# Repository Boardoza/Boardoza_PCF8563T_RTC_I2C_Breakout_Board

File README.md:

# Boardoza PCF8563T RTC Breakout Board

The **Boardoza PCF8563T RTC Breakout Board** is a compact and reliable real-time clock solution built around the **PCF8563T** low-power CMOS clock/calendar IC from NXP. It provides accurate timekeeping with full calendar functionality including year, month, day, weekday, hours, minutes, and seconds. Designed for embedded systems that require dependable time management.

With its simple I²C interface and clearly labeled header pins, this breakout board is fully compatible with Arduino, Raspberry Pi, STM32, ESP32, and other microcontrollers that **support I²C communication**. It is ideal for applications such as **data logging, alarm scheduling, time-stamping systems, industrial controllers, IoT devices, and battery-powered embedded projects.**

> [!WARNING]
> This product does not come with a CR1220 coin cell battery. The battery must be purchased separately.

## [Click here to purchase!](https://www.ozdisan.com/ureticiler/boardoza)

| Front Side | Back Side |
|:---:|:---:|
|  |  |

---

## Key Features

- **Accurate Real-Time Clock:** Maintains precise time and full calendar tracking.
- **I²C Interface:** Simple and widely supported communication with microcontrollers.
- **Interrupt & Clock Output:** Provides **nINT** for alerts and **CLK_O** for clock signal output.
- **Battery Backup Support:** Continues timekeeping during power loss with a coin cell battery.
- **Wide Compatibility:** Works with Arduino, ESP32, STM32, Raspberry Pi, and more.

---

## Technical Specifications

**Model:** PCF8563T  
**Manufacturer:** Boardoza    
**Manufacturer IC:** NXP Semiconductors  
**Input Voltage:** 2.5V – 5.5V DC  
**Functions:** Real-Time Clock & Calendar  
**Communication:** I²C (7-bit address 0x51, Write: A2h, Read: A3h)  
**Oscillator Frequency:** 32.768 kHz  
**Operating Temperature:** -40°C to +85°C  
**Board Dimensions:** 20mm x 20mm  

---

## Board Pinout

### ( J1 ) Main Connector

| Pin Number | Pin Name | Description |
|:---:|:---:|---|
| 1 | VCC | Supply Voltage |
| 2 | nINT | Interrupt Output (Active Low) |
| 3 | SDA | I²C Serial Data Pin |
| 4 | SCL | I²C Serial Clock Pin |
| 5 | CLK_O | Clock Output |
| 6 | GND | Ground |

---

## Board Dimensions

---

## Step Files

[Boardoza PCF8563T.step](./assets/PCF8563T%20Step.step)

---

## Datasheet

[PCF8563T Datasheet](./assets/PCF8563T%20Datasheet.pdf)

---

## Version History

- V1.0.0 - Initial Release

---

## Support

- If you have any questions or need support, please contact support@boardoza.com

---

## **License**

This repository contains both hardware and software components:

### **Hardware Design**

[![CC BY-SA 4.0][cc-by-sa-shield]][cc-by-sa]

All hardware design files are licensed under [Creative Commons Attribution-ShareAlike 4.0 International License][cc-by-sa].

[cc-by-sa]: http://creativecommons.org/licenses/by-sa/4.0/
[cc-by-sa-shield]: https://img.shields.io/badge/License-CC%20BY--SA%204.0-lightgrey.svg

### **Software/Firmware**

[![BSD-3-Clause][bsd-shield]][bsd]

All software and firmware are licensed under [BSD 3-Clause License][bsd].

[bsd]: https://opensource.org/licenses/BSD-3-Clause
[bsd-shield]: https://img.shields.io/badge/License-BSD%203--Clause-blue.svg

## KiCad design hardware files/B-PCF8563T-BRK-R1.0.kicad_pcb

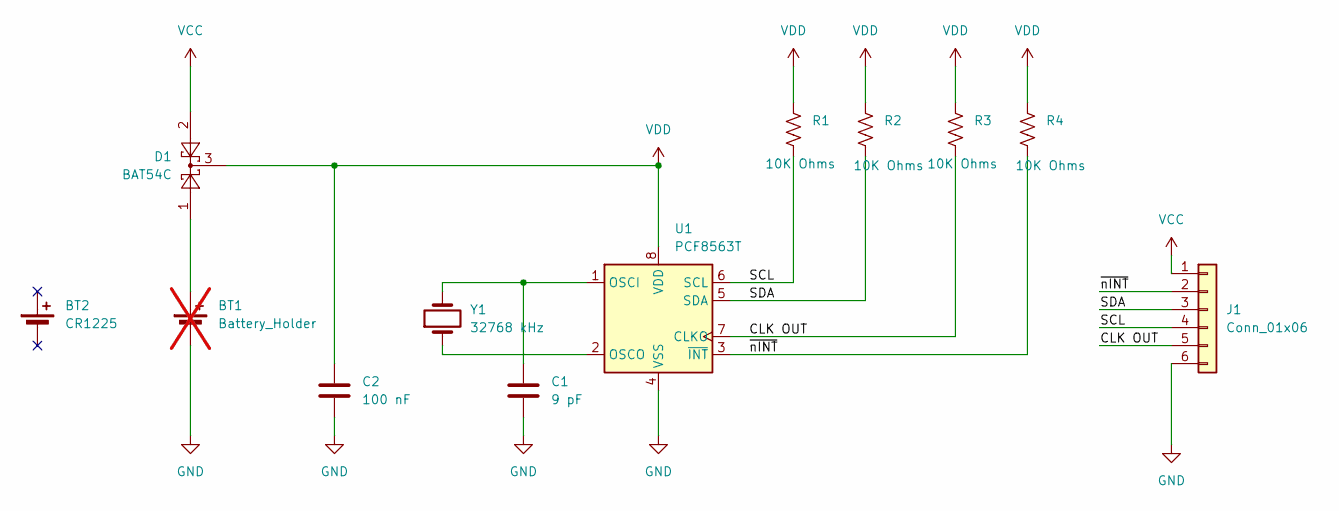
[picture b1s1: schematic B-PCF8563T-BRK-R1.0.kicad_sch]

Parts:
BT1: Battery_Holder; BatteryHolder_LINX_BAT-HLD-012-SMT; MPN L-KLS5-CR1220-011-R; not fitted
BT2: CR1225; BatteryHolder_LINX_BAT-HLD-012-SMT; MPN CR1225 PARA PİL
C1: 9 pF; C_0603_1608Metric; MPN CC0603CRNPO9BN9R0
C2: 100 nF; C_0603_1608Metric; MPN MCF03KTB500104
D1: BAT54C; SOT-23; MPN BAT54C,215
J1: Conn_01x06; Connector 1x6; MPN 2317-06S
R1, R2, R3, R4: 10K Ohms; R_0603_1608Metric; MPN CRT03J7E1002
U1: PCF8563T; SOIC-8_3.9x4.9mm_P1.27mm; MPN PCF8563T/5,518
Y1: 32768 kHz; Xtal 32768 kHz; MPN Q 0.032768 JTX310-12,5-1

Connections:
/CLK OUT: J1.5, R3.2, U1.7 (CLKO)
/SCL: J1.4, R1.2, U1.6 (SCL)
/SDA: J1.3, R2.2, U1.5 (SDA)
/~nINT: J1.2, R4.2, U1.3 (~INT)
GND: BT1.2 (-), C1.2, C2.2, J1.6, U1.4 (VSS)
unnamed: BT1.1 (+), D1.1
unnamed: C1.1, U1.1 (OSCI), Y1.2
unnamed: U1.2 (OSCO), Y1.1
VCC: D1.2, J1.1
VDD: C2.1, D1.3, R1.1, R2.1, R3.1, R4.1, U1.8 (VDD)

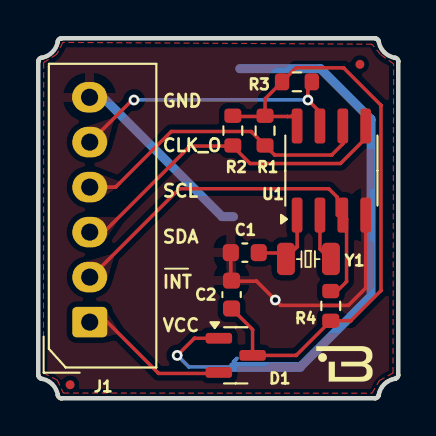
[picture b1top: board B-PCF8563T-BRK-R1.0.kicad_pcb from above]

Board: 2 copper layers, 20.0 x 20.0 mm, 11 parts (1 on the bottom side), 10 nets.
